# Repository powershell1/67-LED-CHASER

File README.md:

# 67-LED-CHASER
I created this project through a Stasis Hack Club workshop. It consists of nine LEDs, a resistor, a timer IC, an LED IC, a capacitor, and a potentiometer.
I plan to start designing PCBs with this project. I normally work on AI, machine learning, and related topics, so I'm excited to try something new.

## Bill of Materials (BOM)
| Item | Quantity | Notes | Price (Est. Total) |
|---|---|---|---|
| Custom PCB board | 1 | You can design this however you want! :) | $4.00 |
| LED | 9 | Depends on your design (approx. $0.10/each) | $0.90 |
| NE555P | 1 | Standard Precision Timer | $0.45 |
| CD4017 | 1 | Decade Counter | $0.55 |
| Female Header, 1x2 | 1 | Receptacle | $0.05 |
| Header, 1x1 | 1 | Male/Female (If you like to debug!) | $0.02 |
| 1uF Capacitor | 1 | Electrolytic | $0.10 |
| 0.01uF Capacitor | 1 | Ceramic Disc | $0.05 |
| 1kΩ Resistor | 1 | 1/4 Watt Metal Film | $0.02 |
| 470Ω Resistor | 1 | 1/4 Watt Metal Film | $0.02 |
| Potentiometer | 1 | Through-hole Trim Pot | $0.60 |
| Estimated Total |  |  | ~$6.76 |

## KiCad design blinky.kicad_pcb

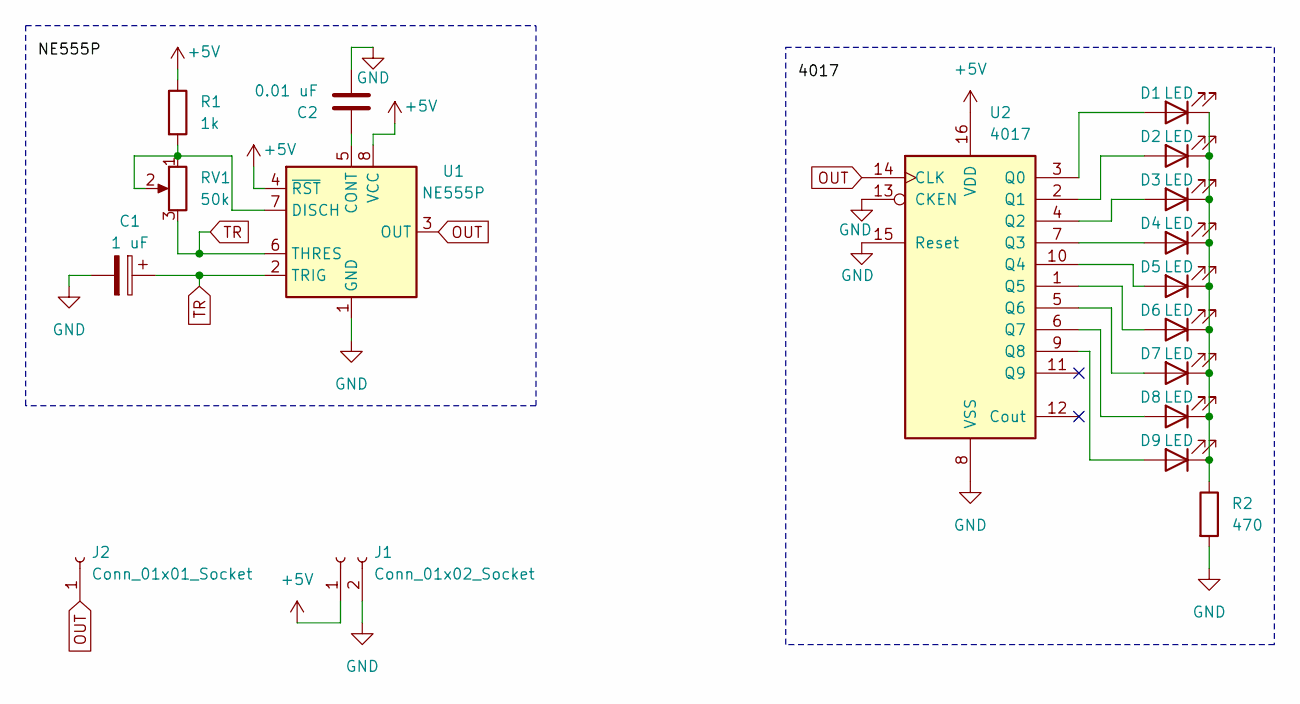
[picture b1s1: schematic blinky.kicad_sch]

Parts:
C1: 1 uF; CP_Radial_D5.0mm_P2.00mm
C2: 0.01 uF; C_Disc_D7.5mm_W2.5mm_P5.00mm
D1, D2, D3, D4, D5, D6, D7, D8, D9: LED; LED_D3.0mm
J1: Conn_01x02_Socket; PinHeader_1x02_P2.54mm_Vertical
J2: Conn_01x01_Socket; PinHeader_1x01_P2.54mm_Vertical
R1: 1k; R_Axial_DIN0207_L6.3mm_D2.5mm_P7.62mm_Horizontal
R2: 470; R_Axial_DIN0207_L6.3mm_D2.5mm_P7.62mm_Horizontal
RV1: 50k; Potentiometer_Vishay_T93YA_Vertical
U1: NE555P; DIP-8_W7.62mm
U2: 4017; N16

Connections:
+5V: J1.1, R1.1, U1.4 (~RST), U1.8 (VCC), U2.16 (VDD)
GND: C1.2, C2.2, J1.2, R2.2, U1.1 (GND), U2.8 (VSS), U2.13 (CKEN), U2.15 (Reset)
unnamed: D1.2 (A), U2.3 (Q0)
unnamed: D1.1 (K), D2.1 (K), D3.1 (K), D4.1 (K), D5.1 (K), D6.1 (K), D7.1 (K), D8.1 (K), D9.1 (K), R2.1
unnamed: D2.2 (A), U2.2 (Q1)
unnamed: D3.2 (A), U2.4 (Q2)
unnamed: D4.2 (A), U2.7 (Q3)
unnamed: D5.2 (A), U2.10 (Q4)
unnamed: D6.2 (A), U2.1 (Q5)
unnamed: D7.2 (A), U2.5 (Q6)
unnamed: D8.2 (A), U2.6 (Q7)
unnamed: D9.2 (A), U2.9 (Q8)
unnamed: C2.1, U1.5 (CONT)
unnamed: R1.2, RV1.1, RV1.2, U1.7 (DISCH)
OUT: J2.1 (Pin_1_1), U1.3 (OUT), U2.14 (CLK)
TR: C1.1, RV1.3, U1.2 (TRIG), U1.6 (THRES)

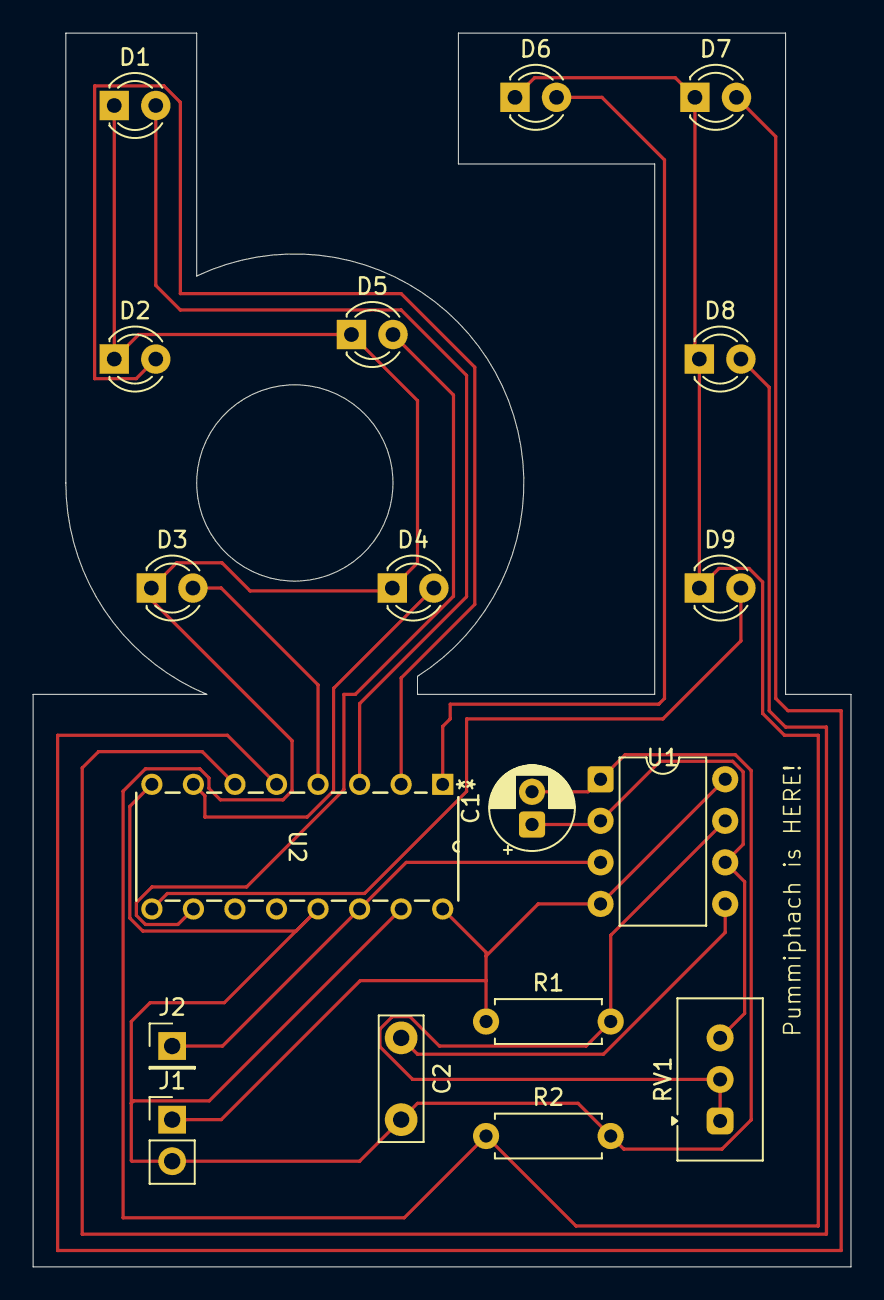
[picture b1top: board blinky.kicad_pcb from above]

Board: 2 copper layers, 50.0 x 75.4 mm, 18 parts (0 on the bottom side), 16 nets.

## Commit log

2026-03-31 Add 3D view image to README
2026-04-01 Enhance README with project details and BOM
    Updated the README to include a Bill of Materials table and additional project details.
2026-04-01 Revise BOM with estimated prices and schematic image
    Updated the Bill of Materials to include estimated prices for each item.
